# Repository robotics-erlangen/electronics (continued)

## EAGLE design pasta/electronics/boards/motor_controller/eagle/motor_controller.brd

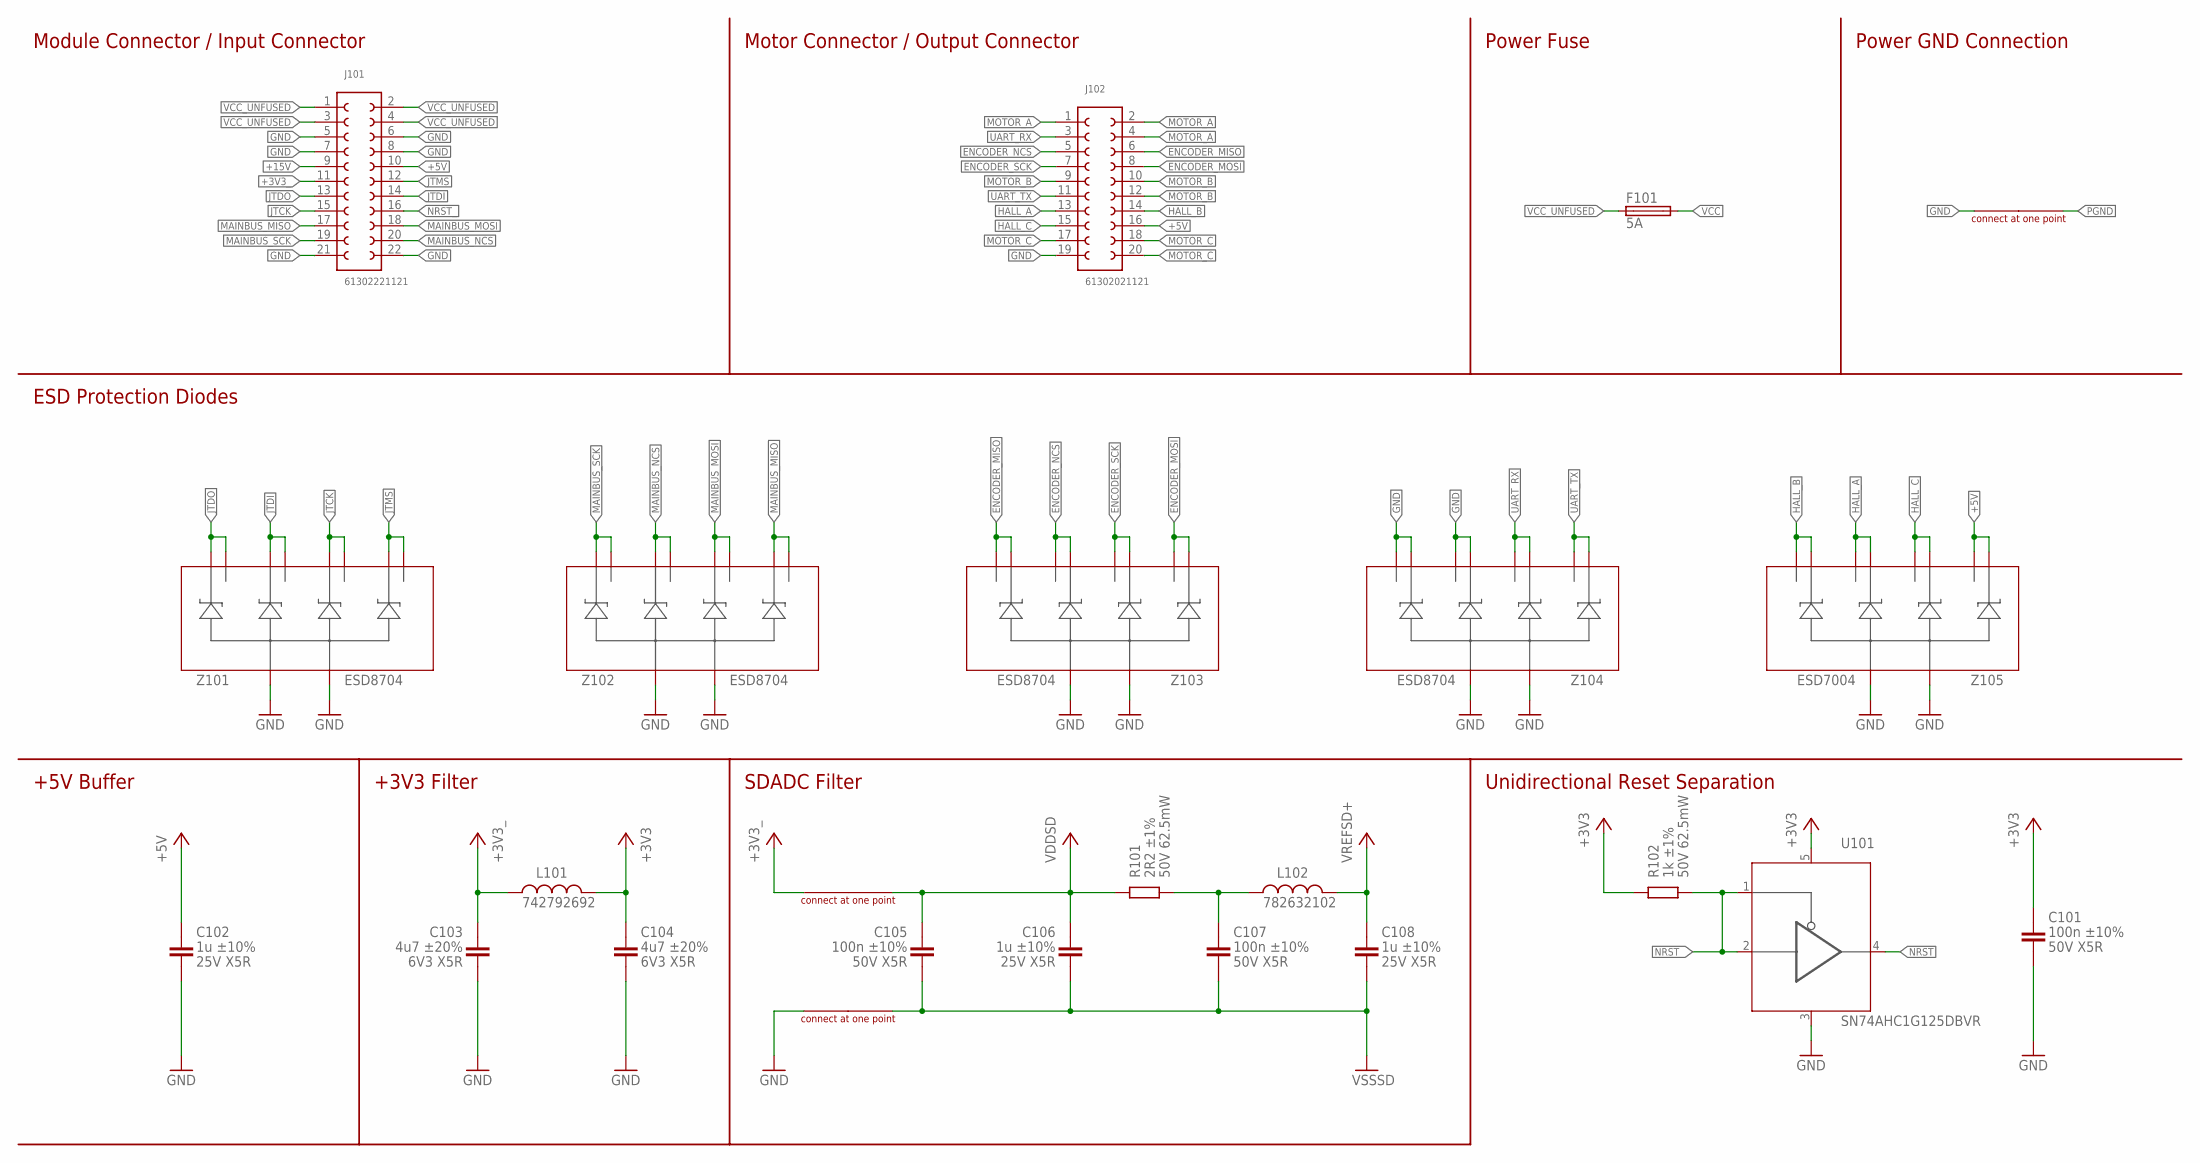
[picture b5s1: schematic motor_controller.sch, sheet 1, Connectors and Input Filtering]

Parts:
C101, C105, C107: 100n ±10% 50V X5R; C0402
C102, C106, C108: 1u ±10% 25V X5R; C0402
C103, C104: 4u7 ±20% 6V3 X5R; C0603
F101: 5A; 157T
J101: 61302221121; HDRV22W64P254_2X11_2794X508X854B
J102: 61302021121; MPN 61302021121
L101: 742792692; WE-CBF_0603(W=2.6)
L102: 782632102; WE-CBF_0603(W=2.6)
R101: 2R2 ±1% 50V 62.5mW; R0402
R102: 1k ±1% 50V 62.5mW; R0402
SHORT101: SHORT4.35
SHORT102, SHORT103: SHORT2.4
U101: SN74AHC1G125DBVR; SOT23-5
Z101, Z102, Z103, Z104: ESD8704; UDFN10
Z105: ESD7004; UDFN10

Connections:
+3V3: C101.1, C104.1, L101.2, R102.1, U101.5 (VCC); also elsewhere on the board
+3V3_: C103.1, J101.11, L101.1, SHORT102.P2
+5V: C102.1, J101.10, J102.16 (13), Z105.1 (C1), Z105.10 (D1)
+15V: J101.9
ENCODER_MISO: J102.6 (18), Z103.5 (C4), Z103.6 (D4); also elsewhere on the board
ENCODER_MOSI: J102.8 (17), Z103.1 (C1), Z103.10 (D1); also elsewhere on the board
ENCODER_NCS: J102.5 (3), Z103.4 (C3), Z103.7 (D3); also elsewhere on the board
ENCODER_SCK: J102.7 (4), Z103.2 (C2), Z103.9 (D2); also elsewhere on the board
GND: C101.2, C102.2, C103.2, C104.2, J101.5, J101.6, J101.7, J101.8, J101.21, J101.22, J102.19 (10), SHORT101.P2, SHORT103.P2, U101.3 (GND), Z101.3 (A), Z101.8 (A), Z102.3 (A), Z102.8 (A), Z103.3 (A), Z103.8 (A), Z104.3 (A), Z104.4 (C3), Z104.5 (C4), Z104.6 (D4), Z104.7 (D3), Z104.8 (A), Z105.3 (A), Z105.8 (A); also elsewhere on the board
HALL_A: J102.13 (7), Z105.4 (C3), Z105.7 (D3); also elsewhere on the board
HALL_B: J102.14, Z105.5 (C4), Z105.6 (D4); also elsewhere on the board
HALL_C: J102.15 (8), Z105.2 (C2), Z105.9 (D2); also elsewhere on the board
JTCK: J101.15, Z101.4 (C3), Z101.7 (D3); also elsewhere on the board
JTDI: J101.14, Z101.2 (C2), Z101.9 (D2); also elsewhere on the board
JTDO: J101.13, Z101.1 (C1), Z101.10 (D1); also elsewhere on the board
JTMS: J101.12, Z101.5 (C4), Z101.6 (D4); also elsewhere on the board
MAINBUS_MISO: J101.17, Z102.5 (C4), Z102.6 (D4); also elsewhere on the board
MAINBUS_MOSI: J101.18, Z102.4 (C3), Z102.7 (D3); also elsewhere on the board
MAINBUS_NCS: J101.20, Z102.2 (C2), Z102.9 (D2); also elsewhere on the board
MAINBUS_SCK: J101.19, Z102.1 (C1), Z102.10 (D1); also elsewhere on the board
MOTOR_A: J102.1, J102.2 (20), J102.4 (19); also elsewhere on the board
MOTOR_B: J102.9 (5), J102.10 (16), J102.12 (15); also elsewhere on the board
MOTOR_C: J102.17 (9), J102.18 (12), J102.20 (11); also elsewhere on the board
unnamed: C107.1, L102.1, R101.2
NRST: U101.4 (O); also elsewhere on the board
NRST_: J101.16, R102.2, U101.1 (OE), U101.2 (I)
PGND: SHORT101.P1; also elsewhere on the board
UART_RX: J102.3 (2), Z104.2 (C2), Z104.9 (D2); also elsewhere on the board
UART_TX: J102.11 (6), Z104.1 (C1), Z104.10 (D1); also elsewhere on the board
VCC: F101.2; also elsewhere on the board
VCC_UNFUSED: F101.1, J101.1, J101.2, J101.3, J101.4
VDDSD: C105.1, C106.1, R101.1, SHORT102.P1; also elsewhere on the board
VREFSD+: C108.1, L102.2; also elsewhere on the board
VSSSD: C105.2, C106.2, C107.2, C108.2, SHORT103.P1; also elsewhere on the board

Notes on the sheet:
Power GND Connection
Module Connector / Input Connector
Motor Connector / Output Connector
Power Fuse
ESD Protection Diodes
+5V Buffer
+3V3 Filter
SDADC Filter
Unidirectional Reset Separation

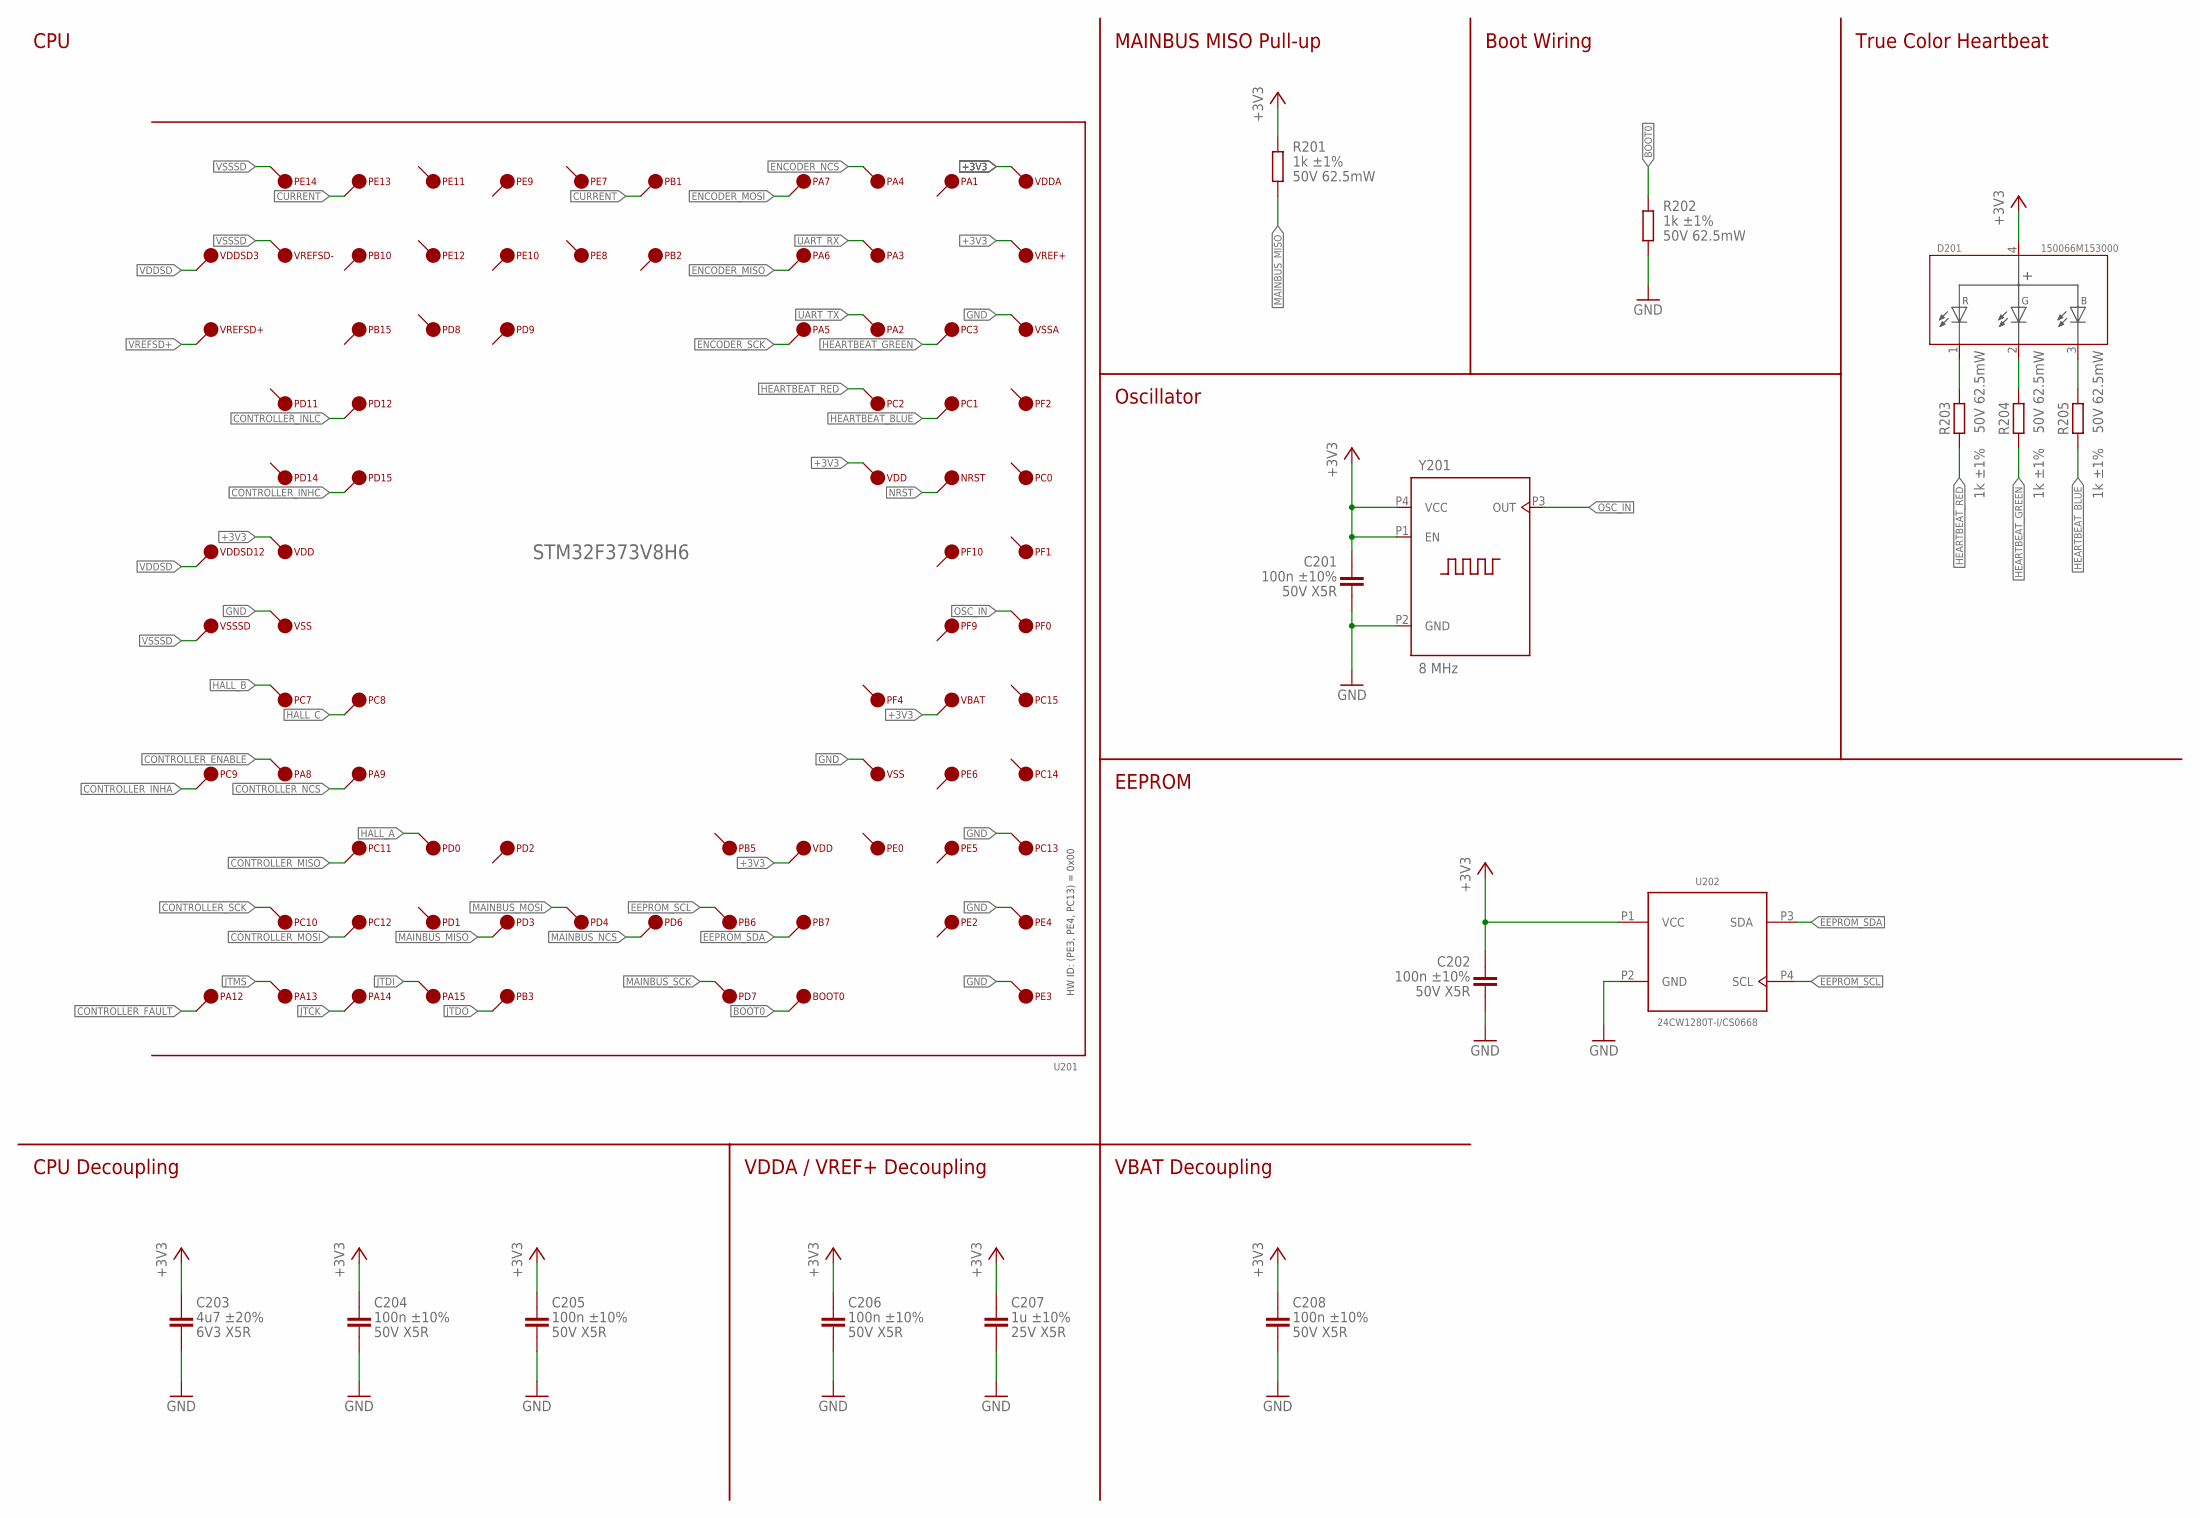
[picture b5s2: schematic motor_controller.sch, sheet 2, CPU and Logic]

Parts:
C201, C202, C204, C205, C206, C208: 100n ±10% 50V X5R; C0402
C203: 4u7 ±20% 6V3 X5R; C0603
C207: 1u ±10% 25V X5R; C0402
D201: 150066M153000; WL-SFCX_0606
R201, R202, R203, R204, R205: 1k ±1% 50V 62.5mW; R0402
U201: STM32F373V8H6
U202: 24CW1280T-I/CS0668; CS0-4
Y201: 8 MHz; 830207192009

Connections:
+3V3: C201.1, C202.1, C203.1, C204.1, C205.1, C206.1, C207.1, C208.1, D201.4, R201.2, U201.VBAT, U201.VDD@1 (VDD), U201.VDD@2 (VDD), U201.VDD@3 (VDD), U201.VDDA, U201.VREF+, U202.P1 (VCC), Y201.P1 (EN), Y201.P4 (VCC); also elsewhere on the board
BOOT0: R202.2, U201.BOOT0
CONTROLLER_ENABLE: U201.PA8; also elsewhere on the board
CONTROLLER_FAULT: U201.PA12; also elsewhere on the board
CONTROLLER_INHA: U201.PC9; also elsewhere on the board
CONTROLLER_INHC: U201.PD15; also elsewhere on the board
CONTROLLER_INLC: U201.PD12; also elsewhere on the board
CONTROLLER_MISO: U201.PC11; also elsewhere on the board
CONTROLLER_MOSI: U201.PC12; also elsewhere on the board
CONTROLLER_NCS: U201.PA9; also elsewhere on the board
CONTROLLER_SCK: U201.PC10; also elsewhere on the board
CURRENT: U201.PB1, U201.PE13; also elsewhere on the board
EEPROM_SCL: U201.PB6, U202.P4 (SCL)
EEPROM_SDA: U201.PB7, U202.P3 (SDA)
ENCODER_MISO: U201.PA6; also elsewhere on the board
ENCODER_MOSI: U201.PA7; also elsewhere on the board
ENCODER_NCS: U201.PA4; also elsewhere on the board
ENCODER_SCK: U201.PA5; also elsewhere on the board
GND: C201.2, C202.2, C203.2, C204.2, C205.2, C206.2, C207.2, C208.2, R202.1, U201.PC13, U201.PE3, U201.PE4, U201.VSS@1 (VSS), U201.VSS@3 (VSS), U201.VSSA, U202.P2 (GND), Y201.P2 (GND); also elsewhere on the board
HALL_A: U201.PD0; also elsewhere on the board
HALL_B: U201.PC7; also elsewhere on the board
HALL_C: U201.PC8; also elsewhere on the board
HEARTBEAT_BLUE: R205.2, U201.PC1
HEARTBEAT_GREEN: R204.2, U201.PC3
HEARTBEAT_RED: R203.2, U201.PC2
JTCK: U201.PA14; also elsewhere on the board
JTDI: U201.PA15; also elsewhere on the board
JTDO: U201.PB3; also elsewhere on the board
JTMS: U201.PA13; also elsewhere on the board
MAINBUS_MISO: R201.1, U201.PD3; also elsewhere on the board
MAINBUS_MOSI: U201.PD4; also elsewhere on the board
MAINBUS_NCS: U201.PD6; also elsewhere on the board
MAINBUS_SCK: U201.PD7; also elsewhere on the board
unnamed: D201.1 (R), R203.1
unnamed: D201.2 (G), R204.1
unnamed: D201.3 (B), R205.1
NRST: U201.NRST; also elsewhere on the board
OSC_IN: U201.PF0, Y201.P3 (OUT)
UART_RX: U201.PA3; also elsewhere on the board
UART_TX: U201.PA2; also elsewhere on the board
VDDSD: U201.VDDSD3, U201.VDDSD12; also elsewhere on the board
VREFSD+: U201.VREFSD+; also elsewhere on the board
VSSSD: U201.PE14, U201.VREFSD-, U201.VSSSD; also elsewhere on the board

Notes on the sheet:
CPU
MAINBUS MISO Pull-up
Boot Wiring
Oscillator
True Color Heartbeat
EEPROM
CPU Decoupling
VDDA / VREF+ Decoupling
VBAT Decoupling
HW ID: (PE3, PE4, PC13) = 0x00

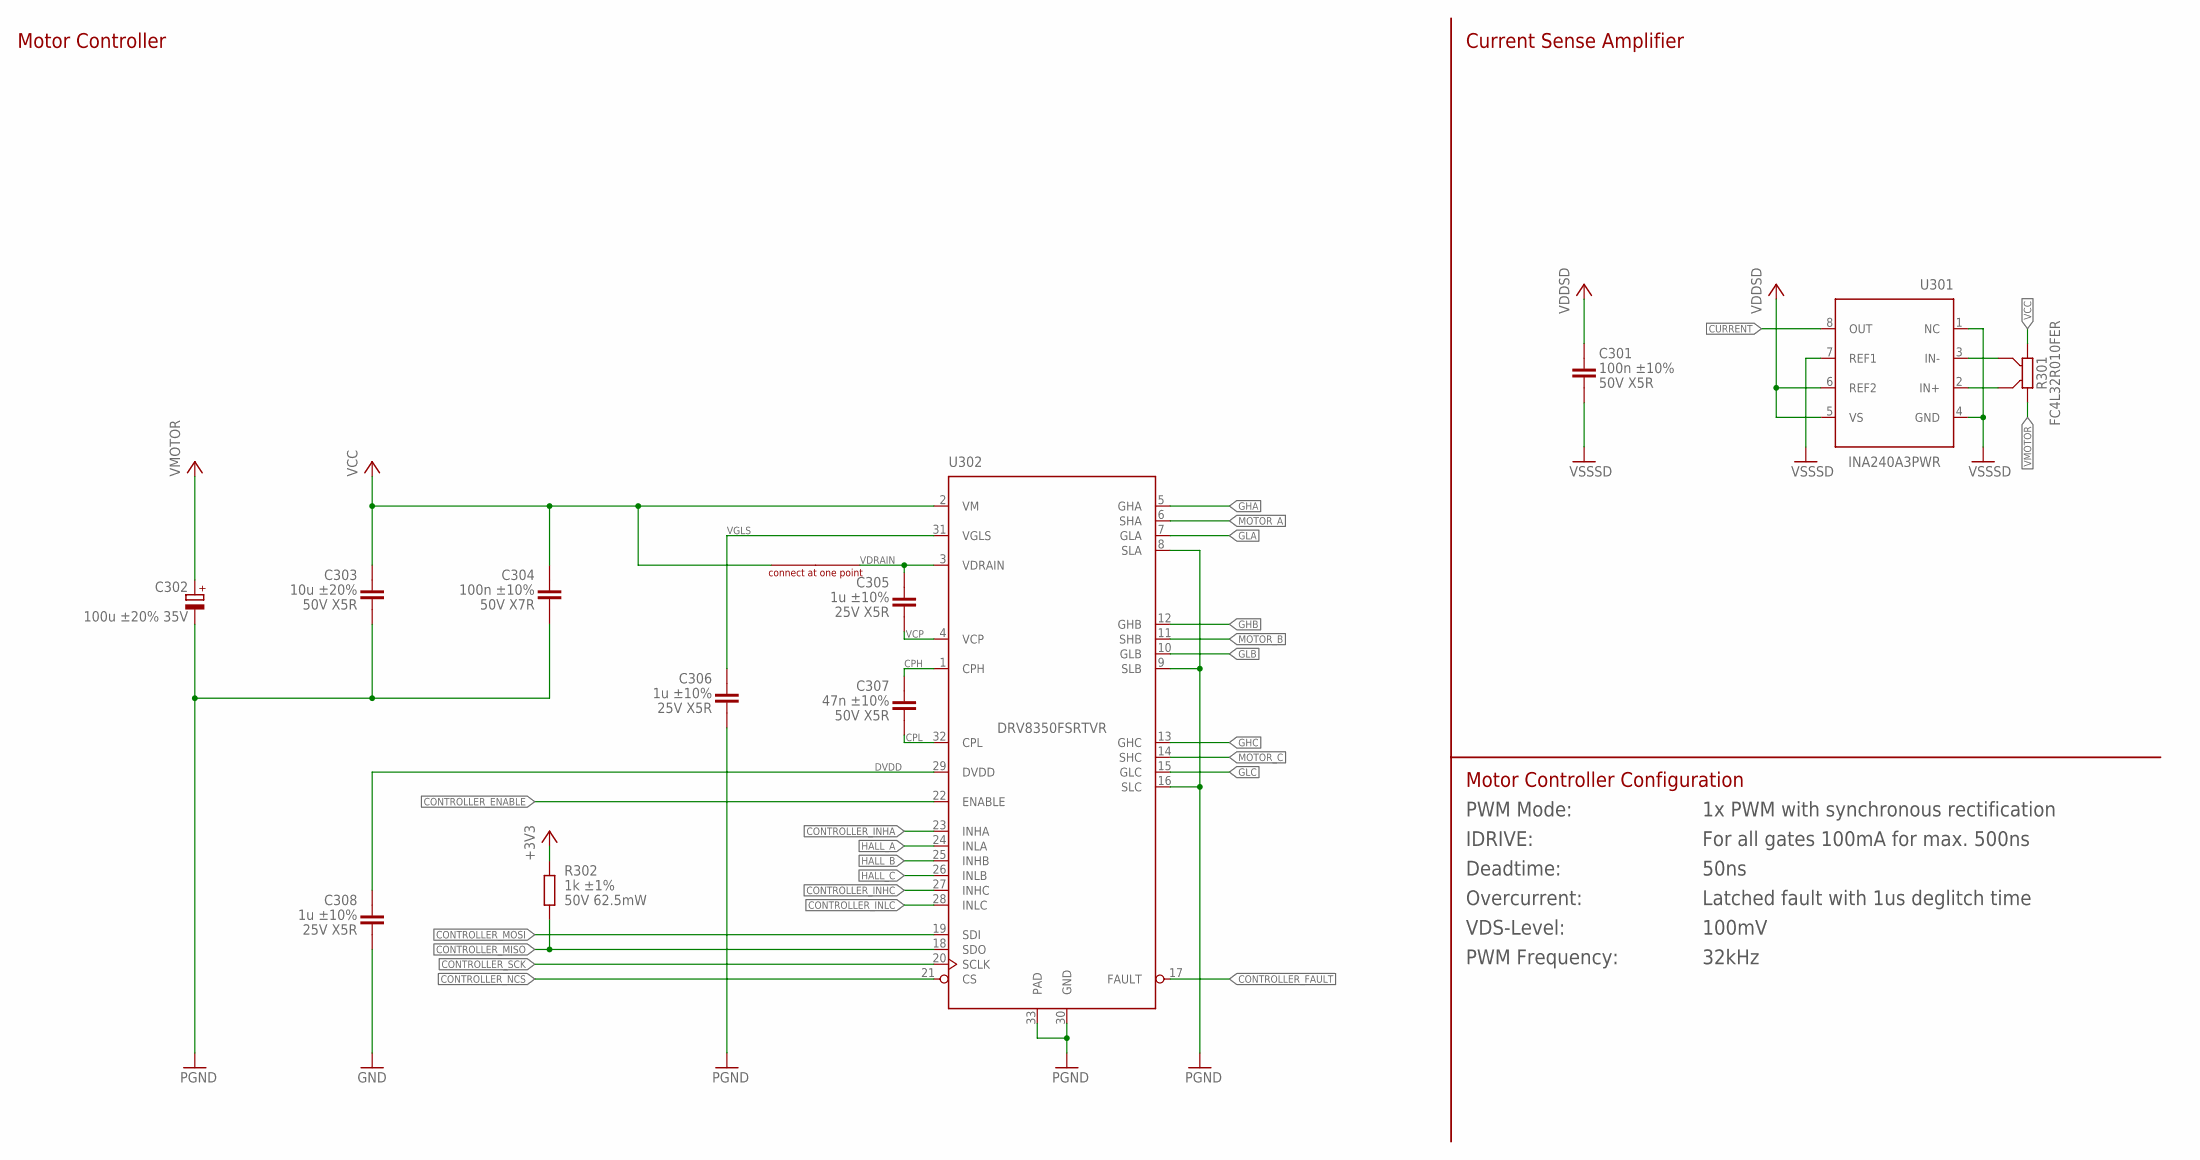
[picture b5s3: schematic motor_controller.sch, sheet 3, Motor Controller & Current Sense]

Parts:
C301: 100n ±10% 50V X5R; C0402
C302: 100u ±20% 35V; 865080545012
C303: 10u ±20% 50V X5R; C1206
C304: 100n ±10% 50V X7R; C0603
C305, C306, C308: 1u ±10% 25V X5R; C0402
C307: 47n ±10% 50V X5R; C0402
R301: FC4L32R010FER; FC4L32
R302: 1k ±1% 50V 62.5mW; R0402
SHORT301: SHORT2.4
U301: INA240A3PWR; TSSOP-8
U302: DRV8350FSRTVR; QFN50P500X500X80-33T345

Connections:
+3V3: R302.2; also elsewhere on the board
CONTROLLER_ENABLE: U302.22 (ENABLE); also elsewhere on the board
CONTROLLER_FAULT: U302.17 (FAULT); also elsewhere on the board
CONTROLLER_INHA: U302.23 (INHA); also elsewhere on the board
CONTROLLER_INHC: U302.27 (INHC); also elsewhere on the board
CONTROLLER_INLC: U302.28 (INLC); also elsewhere on the board
CONTROLLER_MISO: R302.1, U302.18 (SDO); also elsewhere on the board
CONTROLLER_MOSI: U302.19 (SDI); also elsewhere on the board
CONTROLLER_NCS: U302.21 (CS); also elsewhere on the board
CONTROLLER_SCK: U302.20 (SCLK); also elsewhere on the board
CPH: C307.1, U302.1 (CPH)
CPL: C307.2, U302.32 (CPL)
CURRENT: U301.8 (OUT); also elsewhere on the board
DVDD: C308.1, U302.29 (DVDD)
GHA: U302.5 (GHA); also elsewhere on the board
GHB: U302.12 (GHB); also elsewhere on the board
GHC: U302.13 (GHC); also elsewhere on the board
GLA: U302.7 (GLA); also elsewhere on the board
GLB: U302.10 (GLB); also elsewhere on the board
GLC: U302.15 (GLC); also elsewhere on the board
GND: C308.2; also elsewhere on the board
HALL_A: U302.24 (INLA); also elsewhere on the board
HALL_B: U302.25 (INHB); also elsewhere on the board
HALL_C: U302.26 (INLB); also elsewhere on the board
MOTOR_A: U302.6 (SHA); also elsewhere on the board
MOTOR_B: U302.11 (SHB); also elsewhere on the board
MOTOR_C: U302.14 (SHC); also elsewhere on the board
unnamed: R301.S1, U301.2 (IN+)
unnamed: R301.S2, U301.3 (IN-)
PGND: C302.N (-), C303.2, C304.2, C306.2, U302.8 (SLA), U302.9 (SLB), U302.16 (SLC), U302.30 (GND), U302.33 (PAD); also elsewhere on the board
VCC: C303.1, C304.1, R301.P2, SHORT301.P1, U302.2 (VM); also elsewhere on the board
VCP: C305.2, U302.4 (VCP)
VDDSD: C301.1, U301.5 (VS), U301.6 (REF2); also elsewhere on the board
VDRAIN: C305.1, SHORT301.P2, U302.3 (VDRAIN)
VGLS: C306.1, U302.31 (VGLS)
VMOTOR: C302.P (+), R301.P1; also elsewhere on the board
VSSSD: C301.2, U301.1 (NC), U301.4 (GND), U301.7 (REF1); also elsewhere on the board

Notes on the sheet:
Motor Controller
Current Sense Amplifier
Motor Controller Configuration
PWM Mode:
IDRIVE:
Deadtime:
Overcurrent:
1x PWM with synchronous rectification
For all gates 100mA for max. 500ns
50ns
Latched fault with 1us deglitch time
VDS-Level:
100mV
PWM Frequency:
32kHz

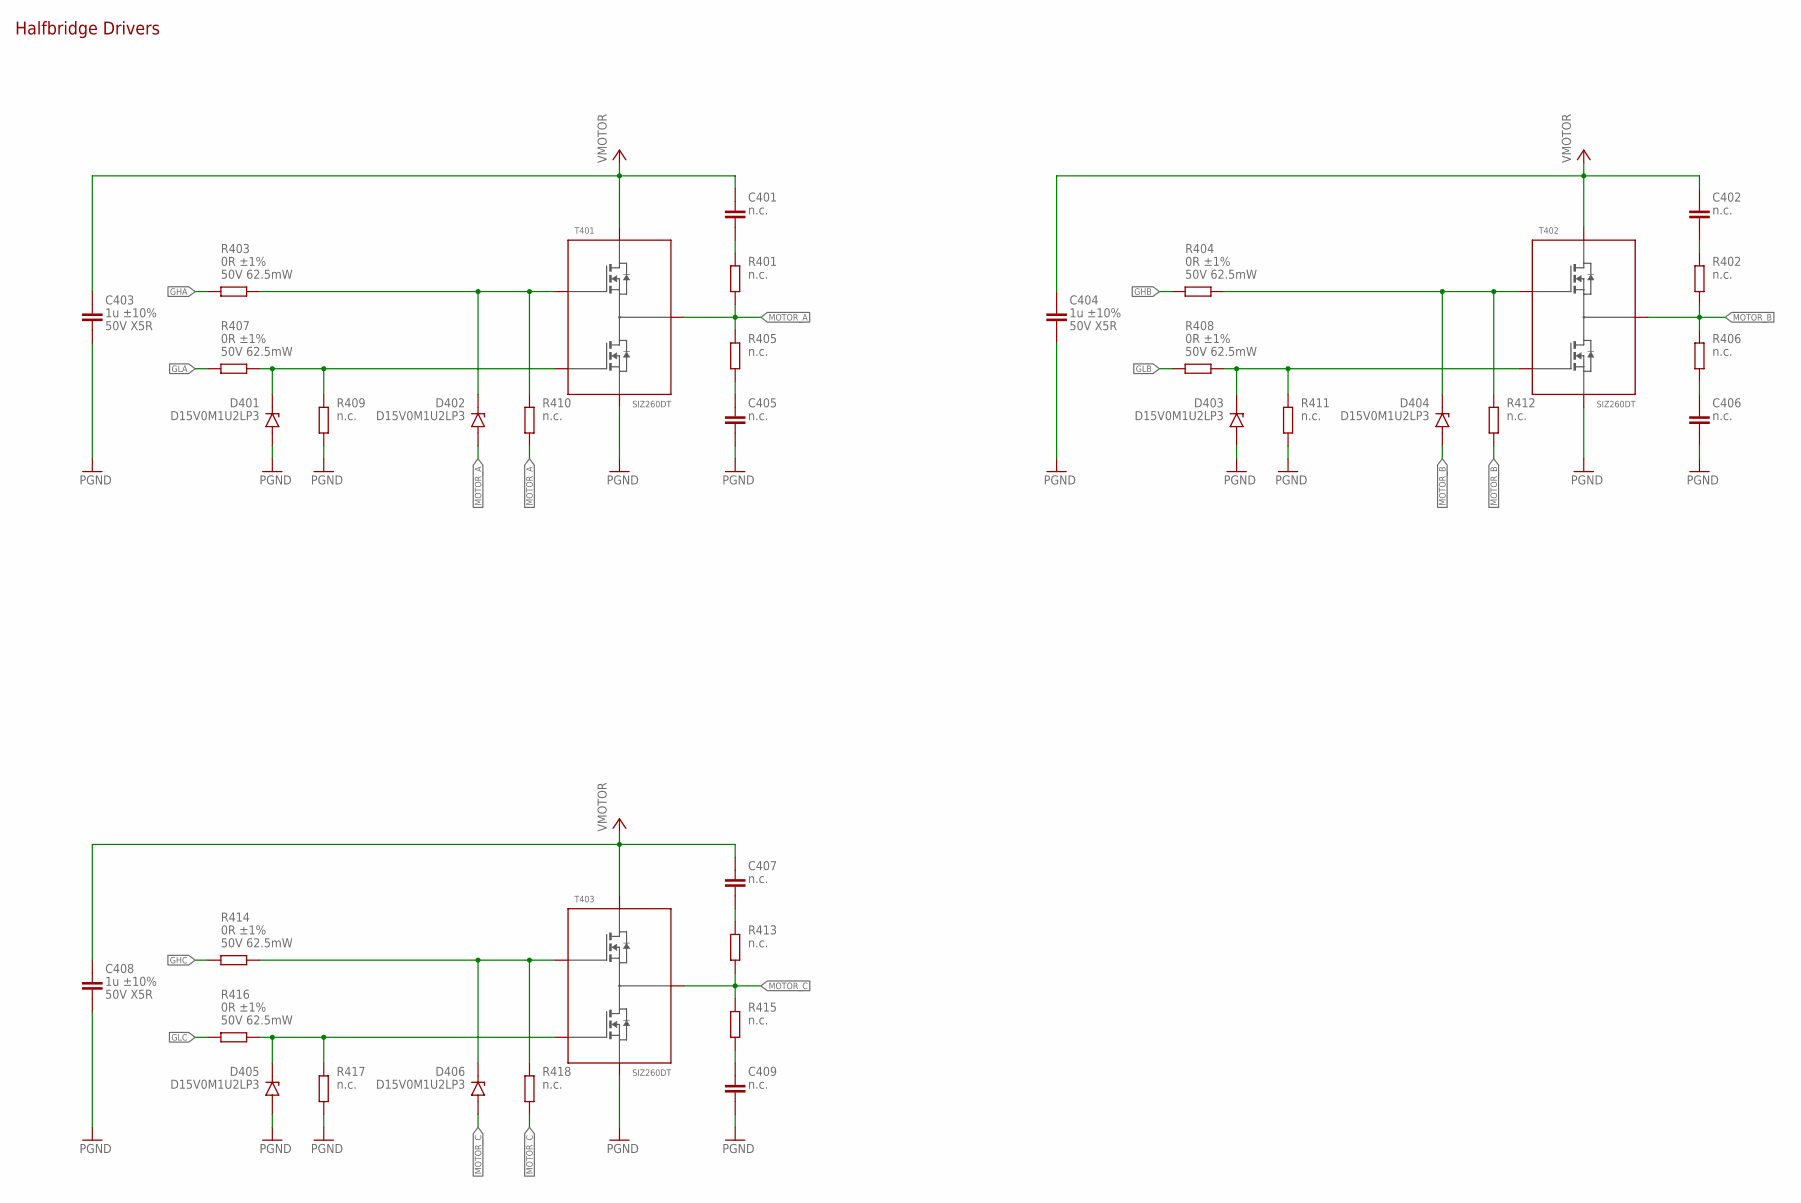
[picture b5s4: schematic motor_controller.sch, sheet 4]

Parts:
C401, C402, C405, C406, C407, C409: n.c.; C0402
C403, C404, C408: 1u ±10% 50V X5R; C0603
D401, D402, D403, D404, D405, D406: D15V0M1U2LP3
R401, R402, R405, R406, R413, R415: n.c.; R0603
R403, R404, R407, R408, R414, R416: 0R ±1% 50V 62.5mW; R0402
R409, R410, R411, R412, R417, R418: n.c.; R0402
T401, T402, T403: SIZ260DT

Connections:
GHA: R403.2; also elsewhere on the board
GHB: R404.2; also elsewhere on the board
GHC: R414.2; also elsewhere on the board
GLA: R407.2; also elsewhere on the board
GLB: R408.2; also elsewhere on the board
GLC: R416.2; also elsewhere on the board
MOTOR_A: D402.P2 (ANODE), R401.1, R405.2, R410.1, T401.P10 (VSW); also elsewhere on the board
MOTOR_B: D404.P2 (ANODE), R402.1, R406.2, R412.1, T402.P10 (VSW); also elsewhere on the board
MOTOR_C: D406.P2 (ANODE), R413.1, R415.2, R418.1, T403.P10 (VSW); also elsewhere on the board
unnamed: C406.1, R406.1
unnamed: D402.P1 (KATHODE), R403.1, R410.2, T401.P1 (GH)
unnamed: C405.1, R405.1
unnamed: C401.2, R401.2
unnamed: C409.1, R415.1
unnamed: D401.P1 (KATHODE), R407.1, R409.2, T401.P8 (GL)
unnamed: C402.2, R402.2
unnamed: D406.P1 (KATHODE), R414.1, R418.2, T403.P1 (GH)
unnamed: D405.P1 (KATHODE), R416.1, R417.2, T403.P8 (GL)
unnamed: C407.2, R413.2
unnamed: D404.P1 (KATHODE), R404.1, R412.2, T402.P1 (GH)
unnamed: D403.P1 (KATHODE), R408.1, R411.2, T402.P8 (GL)
PGND: C403.2, C404.2, C405.2, C406.2, C408.2, C409.2, D401.P2 (ANODE), D403.P2 (ANODE), D405.P2 (ANODE), R409.1, R411.1, R417.1, T401.P5 (PGND), T401.P6 (PGND), T401.P7 (PGND), T402.P5 (PGND), T402.P6 (PGND), T402.P7 (PGND), T403.P5 (PGND), T403.P6 (PGND), T403.P7 (PGND); also elsewhere on the board
VMOTOR: C401.1, C402.1, C403.1, C404.1, C407.1, C408.1, T401.P2 (VIN), T401.P3 (VIN), T401.P4 (VIN), T401.P9 (VIN), T402.P2 (VIN), T402.P3 (VIN), T402.P4 (VIN), T402.P9 (VIN), T403.P2 (VIN), T403.P3 (VIN), T403.P4 (VIN), T403.P9 (VIN); also elsewhere on the board

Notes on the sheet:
Halfbridge Drivers

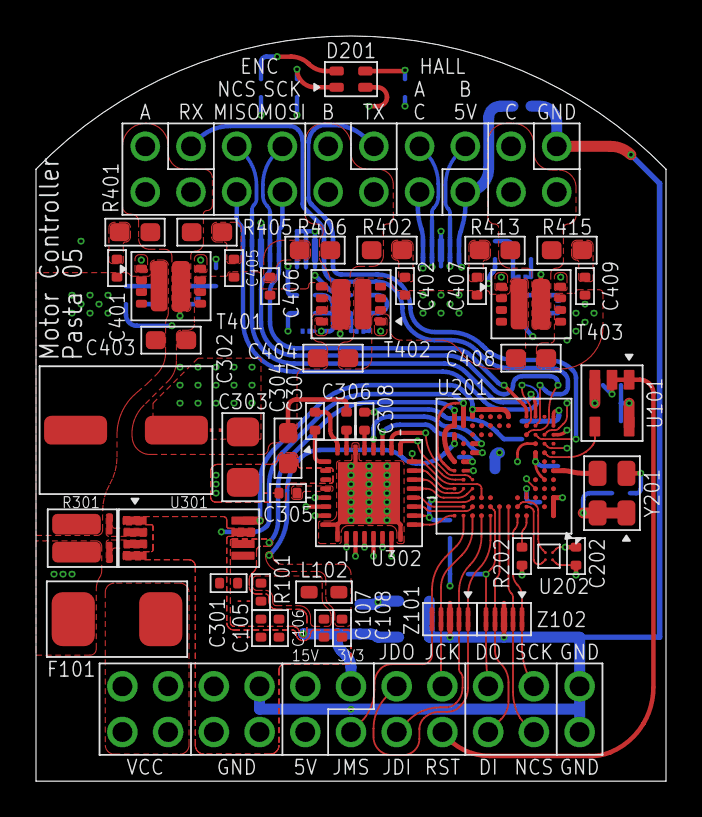
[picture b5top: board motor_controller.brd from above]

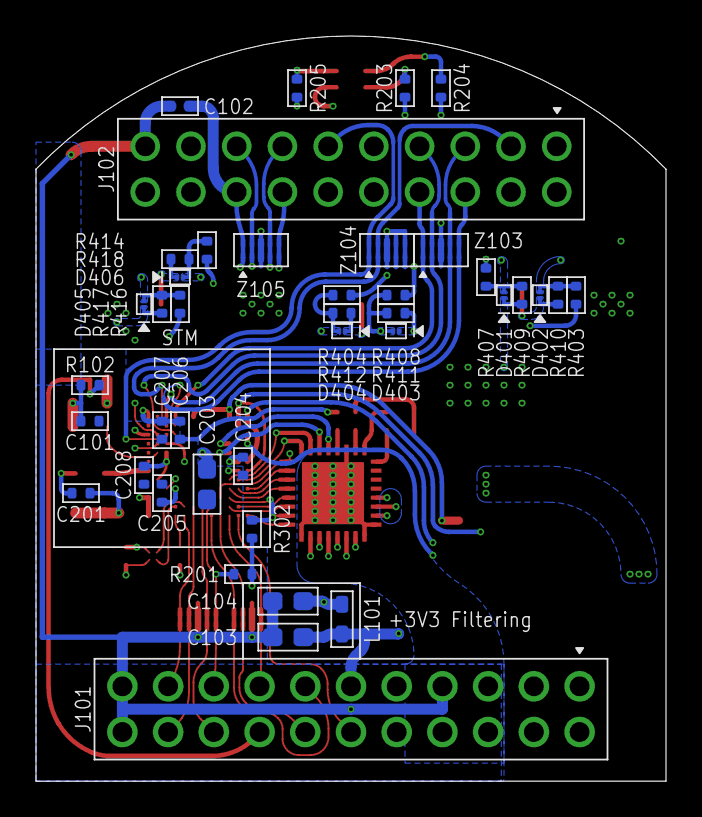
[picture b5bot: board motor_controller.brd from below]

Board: 4 copper layers, 35.0 x 41.4 mm, 90 parts (41 on the bottom side), 80 nets.

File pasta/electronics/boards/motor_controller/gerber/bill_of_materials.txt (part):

Stückliste exportiert aus D:/hardware/pasta/electronics/boards/motor_controller/eagle/motor_controller.sch am 04.07.2023 13:00

Part     Value              Device                   Package                          Description                                                                    CAPACITANCE DIELECTRIC DIGIKEY      FARNELL LINE1     LINE2      MF                   MOUSER               MPN                POWER  RESISTANCE RS-ONLINE TOLERANCE VALUE              VOLTAGE
C101     100n ±10% 50V X5R  C(100NF,50V,0402)        C0402                            Robotics Erlangen Capacitor Library                                            100n        X5R                             100n ±10% 50V X5R    Murata Electronics                        GRM155R61H104KE14J                             ±10%      100n ±10% 50V X5R  50V    
C102     1u ±10% 25V X5R    C(1.0UF,25V,0402)        C0402                            Robotics Erlangen Capacitor Library                                            1u          X5R                             1u ±10%   25V X5R    Murata Electronics                        GRM155R61E105KA12D                             ±10%      1u ±10% 25V X5R    25V    
C103     4u7 ±20% 6V3 X5R   C(4.7UF,6.3V,0603)       C0603                            Robotics Erlangen Capacitor Library                                            4u7         X5R                             4u7 ±20%  6V3 X5R    Würth Elektronik                          885012106005                                   ±20%      4u7 ±20% 6V3 X5R   6V3    
C104     4u7 ±20% 6V3 X5R   C(4.7UF,6.3V,0603)       C0603                            Robotics Erlangen Capacitor Library                                            4u7         X5R                             4u7 ±20%  6V3 X5R    Würth Elektronik                          885012106005                                   ±20%      4u7 ±20% 6V3 X5R   6V3    
C105     100n ±10% 50V X5R  C(100NF,50V,0402)        C0402                            Robotics Erlangen Capacitor Library                                            100n        X5R                             100n ±10% 50V X5R    Murata Electronics                        GRM155R61H104KE14J                             ±10%      100n ±10% 50V X5R  50V    
C106     1u ±10% 25V X5R    C(1.0UF,25V,0402)        C0402                            Robotics Erlangen Capacitor Library                                            1u          X5R                             1u ±10%   25V X5R    Murata Electronics                        GRM155R61E105KA12D                             ±10%      1u ±10% 25V X5R    25V    
C107     100n ±10% 50V X5R  C(100NF,50V,0402)        C0402                            Robotics Erlangen Capacitor Library                                            100n        X5R                             100n ±10% 50V X5R    Murata Electronics                        GRM155R61H104KE14J                             ±10%      100n ±10% 50V X5R  50V    
C108     1u ±10% 25V X5R    C(1.0UF,25V,0402)        C0402                            Robotics Erlangen Capacitor Library                                            1u          X5R                             1u ±10%   25V X5R    Murata Electronics                        GRM155R61E105KA12D                             ±10%      1u ±10% 25V X5R    25V    
C201     100n ±10% 50V X5R  C(100NF,50V,0402)        C0402                            Robotics Erlangen Capacitor Library                                            100n        X5R                             100n ±10% 50V X5R    Murata Electronics                        GRM155R61H104KE14J                             ±10%      100n ±10% 50V X5R  50V    
C202     100n ±10% 50V X5R  C(100NF,50V,0402)        C0402                            Robotics Erlangen Capacitor Library                                            100n        X5R                             100n ±10% 50V X5R    Murata Electronics                        GRM155R61H104KE14J                             ±10%      100n ±10% 50V X5R  50V    
C203     4u7 ±20% 6V3 X5R   C(4.7UF,6.3V,0603)       C0603                            Robotics Erlangen Capacitor Library                                            4u7         X5R                             4u7 ±20%  6V3 X5R    Würth Elektronik                          885012106005                                   ±20%      4u7 ±20% 6V3 X5R   6V3    
C204     100n ±10% 50V X5R  C(100NF,50V,0402)        C0402                            Robotics Erlangen Capacitor Library                                            100n        X5R                             100n ±10% 50V X5R    Murata Electronics                        GRM155R61H104KE14J                             ±10%      100n ±10% 50V X5R  50V    
C205     100n ±10% 50V X5R  C(100NF,50V,0402)        C0402                            Robotics Erlangen Capacitor Library                                            100n        X5R                             100n ±10% 50V X5R    Murata Electronics                        GRM155R61H104KE14J                             ±10%      100n ±10% 50V X5R  50V    
C206     100n ±10% 50V X5R  C(100NF,50V,0402)        C0402                            Robotics Erlangen Capacitor Library                                            100n        X5R                             100n ±10% 50V X5R    Murata Electronics                        GRM155R61H104KE14J                             ±10%      100n ±10% 50V X5R  50V    
C207     1u ±10% 25V X5R    C(1.0UF,25V,0402)        C0402                            Robotics Erlangen Capacitor Library                                            1u          X5R                             1u ±10%   25V X5R    Murata Electronics                        GRM155R61E105KA12D                             ±10%      1u ±10% 25V X5R    25V    
C208     100n ±10% 50V X5R  C(100NF,50V,0402)        C0402                            Robotics Erlangen Capacitor Library                                            100n        X5R                             100n ±10% 50V X5R    Murata Electronics                        GRM155R61H104KE14J                             ±10%      100n ±10% 50V X5R  50V    
C301     100n ±10% 50V X5R  C(100NF,50V,0402)        C0402                            Robotics Erlangen Capacitor Library                                            100n        X5R                             100n ±10% 50V X5R    Murata Electronics                        GRM155R61H104KE14J                             ±10%      100n ±10% 50V X5R  50V    
C302     100u ±20% 35V      865080545012             865080545012                                                                                                                                                                     Würth Elektronik                          865080545012                                             100u ±20% 35V             
C303     10u ±20% 50V X5R   C(10UF,50V,1206)         C1206                            Robotics Erlangen Capacitor Library                                            10u         X5R                             10u ±20%  50V X5R    Samsung                                   CL31A106MBHNNNE                                ±20%      10u ±20% 50V X5R   50V    
C304     100n ±10% 50V X7R  C(100NF,50V,0603)        C0603                            Robotics Erlangen Capacitor Library                                            100n        X7R                             100n ±10% 50V X7R    Würth Elektronik                          885012206095                                   ±10%      100n ±10% 50V X7R  50V    
C305     1u ±10% 25V X5R    C(1.0UF,25V,0402)        C0402                            Robotics Erlangen Capacitor Library                                            1u          X5R                             1u ±10%   25V X5R    Murata Electronics                        GRM155R61E105KA12D                             ±10%      1u ±10% 25V X5R    25V    
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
